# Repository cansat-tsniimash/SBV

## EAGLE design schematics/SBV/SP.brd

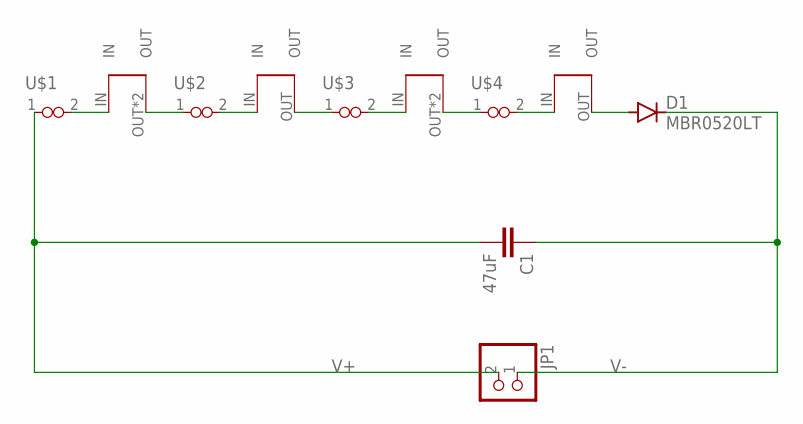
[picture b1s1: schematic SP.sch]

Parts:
C1: 47uF; C1210
D1: MBR0520LT; SOD123
JP1: PINHD-1X2; 1X02
U$1, U$2, U$3, U$4: VIAS-CONNECT
U$5, U$8: SOLAR_1
U$6, U$7: SOLAR_0

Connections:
unnamed: U$1.2, U$7.IN
unnamed: U$2.1, U$7.OUT, U$7.OUT-21 (OUT)
unnamed: U$2.2, U$5.IN
unnamed: D1.A, U$8.OUT
unnamed: U$3.1, U$5.OUT
unnamed: U$3.2, U$6.IN
unnamed: U$4.1, U$6.OUT, U$6.OUT-21 (OUT)
unnamed: U$4.2, U$8.IN
V+: C1.2, JP1.2, U$1.1
V-: C1.1, D1.C, JP1.1

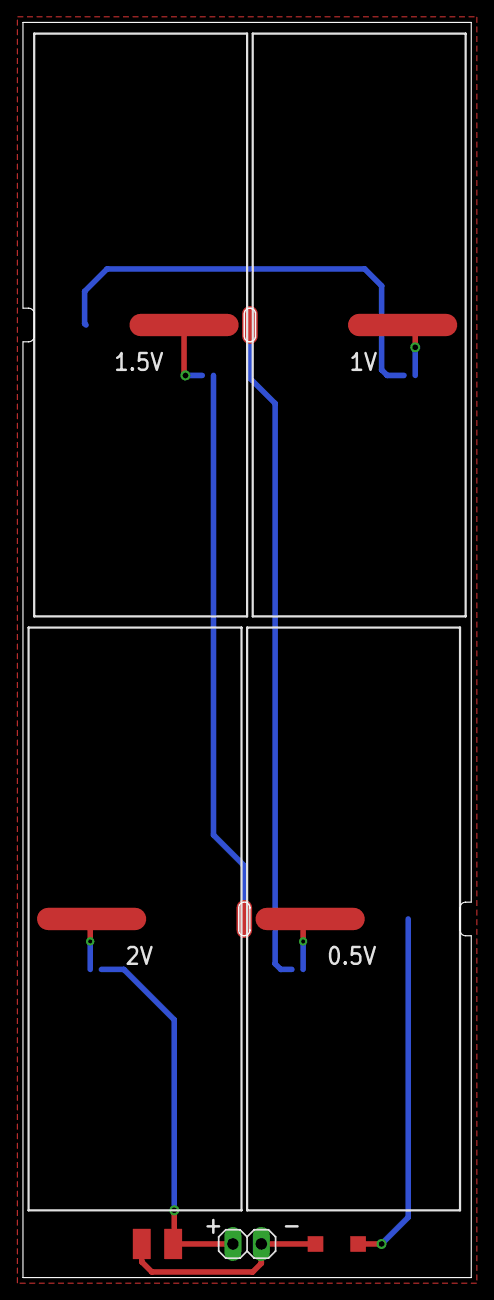
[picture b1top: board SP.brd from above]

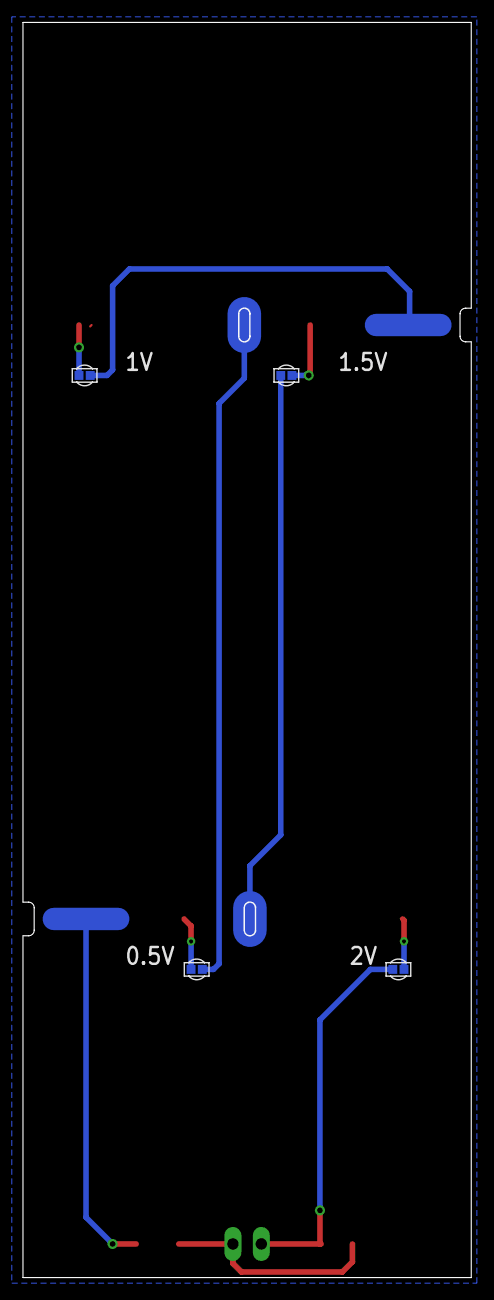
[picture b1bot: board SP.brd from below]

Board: 2 copper layers, 40.0 x 111.9 mm, 11 parts (4 on the bottom side), 10 nets.

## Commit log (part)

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2025-12-09 initial
2026-02-11 Чето сделал для ванваера
2026-02-11 Добавил схему для супер пупер кансата (рабочее имя - Инокентий)
2026-02-14 Дописали драйвер ds18b20. ДСка работает
2026-02-21 я сделал очень крутую штуку по имени наземка
2026-02-21 я всё сломал и всё поченил что сохранять и читать
2026-02-28 Написали прием GPS. Пока не ловили спутники
2026-02-28 Почти написали BMP280
2026-03-07 Написали lsm
2026-03-07 ЗАБЫТЫЕ ФАЙЛЫ
2026-03-07 начали писать lis2mdl
2026-03-14 Частично написали драйвер для SDкарты
2026-03-18 переписали SD карту
2026-03-21 частично написали LORA
2026-03-25 Написали лору но еще не тестили
2026-03-28 чтото сделал
2026-03-28 добавил часть кода для расшифровки нашего пакета
2026-03-28 Исправил ГРУБЕЙШУЮ ОШИБКУ
2026-04-07 попытка написать регистры ины
2026-04-07 начал писать ину
2026-04-08 поправки в радио
2026-04-11 Начал писать фоторезы, дополнил цикл работы, начал передавать данные с датчиков в пакете
2026-04-11 Добавил камиты
2026-04-11 мне сказали я исправил
2026-04-11 я наконецто написал наземку
2026-04-11 Минус строчка
2026-04-11 подправил попугаев
2026-04-11 Поправила датчики, добавила комментарии
2026-05-11 много чего сделал написал ину сервы и частично фоторезы
2026-05-11 Написал базовое наведение
2026-05-12 Доработал алгоритм. Сохраняю код перед жоскими перестановками в коде =)
2026-05-12 Почти дописал алгоритм
2026-05-16 Прога практически написана, максимум осталось поправить баги если такие найдутся
2026-05-20 Написал второй акселирометр
2026-05-29 Ну какие то там изменения есть наверное
2026-06-09 ЭКСТРЕННО ВСЕ КОММИЧУ ато меня побьют
2026-06-09 Налажена работа второй ины
2026-06-19 Что-то сломалось
2026-06-19 Немножечко изменили код, общее перенесли в меджик, и сделали так, что все данные сохраняются
